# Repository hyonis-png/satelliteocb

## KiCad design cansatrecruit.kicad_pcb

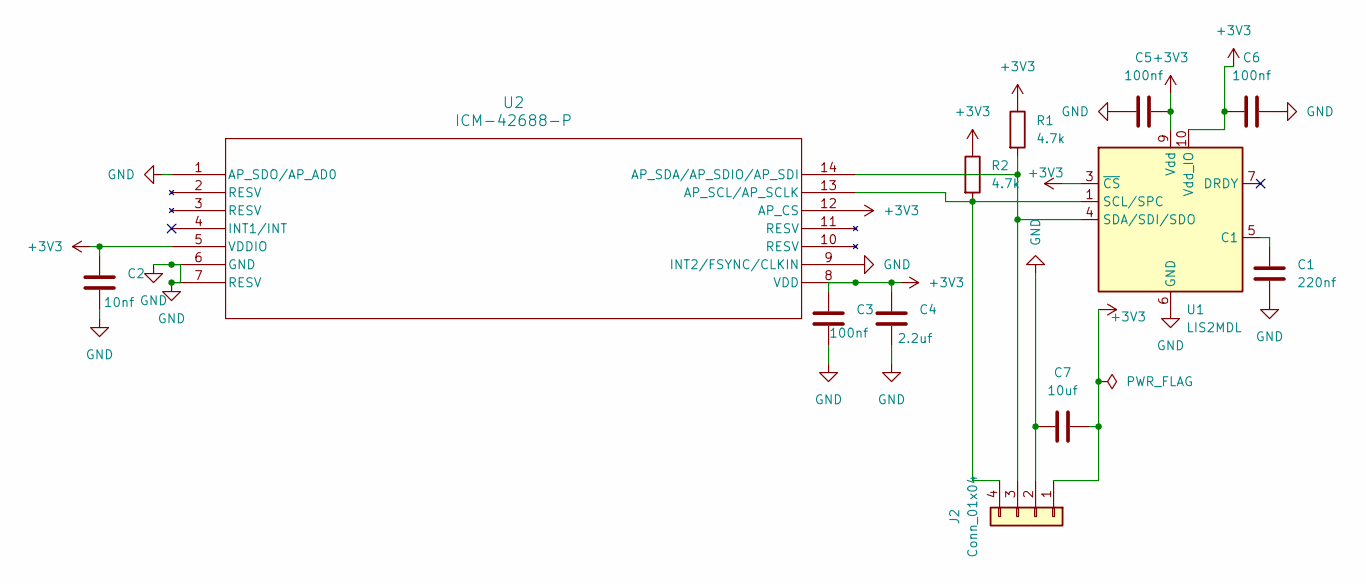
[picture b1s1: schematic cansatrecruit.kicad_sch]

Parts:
C1: 220nf; C_0603_1608Metric
C2: 10nf; C_0603_1608Metric
C3, C5, C6: 100nf; C_0603_1608Metric
C4: 2.2uf; C_0603_1608Metric
C7: 10uf; C_0805_2012Metric
J2: Conn_01x04; PinHeader_1x04_P2.54mm_Vertical
R1, R2: 4.7k; R_0603_1608Metric
U1: LIS2MDL; LGA-12_2x2mm_P0.5mm
U2: ICM-42688-P; LGA-14_3x2.5mm_P0.5mm_LayoutBorder3x4y

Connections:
+3V3: C2.1, C3.1, C4.1, C5.1, C6.1, C7.2, J2.1, R1.1, R2.1, U1.3 (~CS), U1.9 (Vdd), U1.10 (Vdd_IO), U2.5 (VDDIO), U2.8 (VDD), U2.12 (AP_CS)
GND: C1.2, C2.2, C3.2, C4.2, C5.2, C6.2, C7.1, J2.2, U1.6 (GND), U1.8 (GND), U2.1 (AP_SDO/AP_AD0), U2.6 (GND), U2.7 (RESV), U2.9 (INT2/FSYNC/CLKIN)
unnamed: J2.3, R1.2, U1.4 (SDA/SDI/SDO), U2.14 (AP_SDA/AP_SDIO/AP_SDI)
unnamed: J2.4, R2.2, U1.1 (SCL/SPC), U2.13 (AP_SCL/AP_SCLK)
unnamed: C1.1, U1.5 (C1)

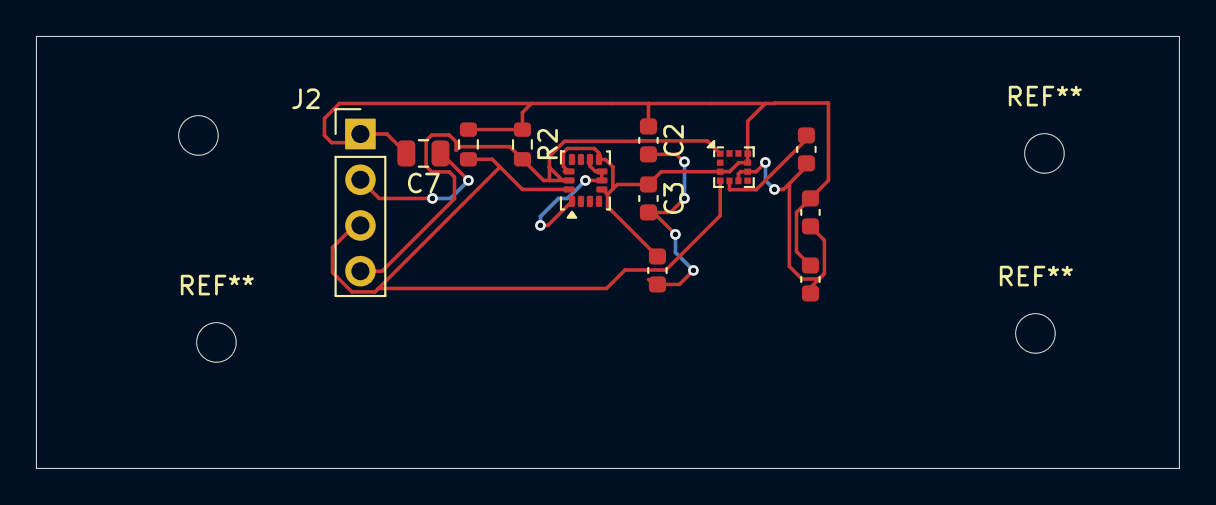
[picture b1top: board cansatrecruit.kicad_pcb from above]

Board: 2 copper layers, 63.5 x 24.0 mm, 12 parts (0 on the bottom side), 5 nets.
